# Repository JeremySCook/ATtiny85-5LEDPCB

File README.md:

# ATtiny85-5LEDPCB
PCB with 5 LEDs, different blinking routines for each.

Manual version: https://www.youtube.com/watch?v=wJXMZybXftk

Auto Light-up Wheel light: https://www.youtube.com/watch?v=zVBrc78851Q

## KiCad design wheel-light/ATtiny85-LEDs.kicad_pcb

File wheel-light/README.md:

KiCAD files for new version using SMD components that activates based on bike wheel's rotation.

Works, but could be improved. ICSP header is connected incorrectly, and battery life is somewhat unknown.

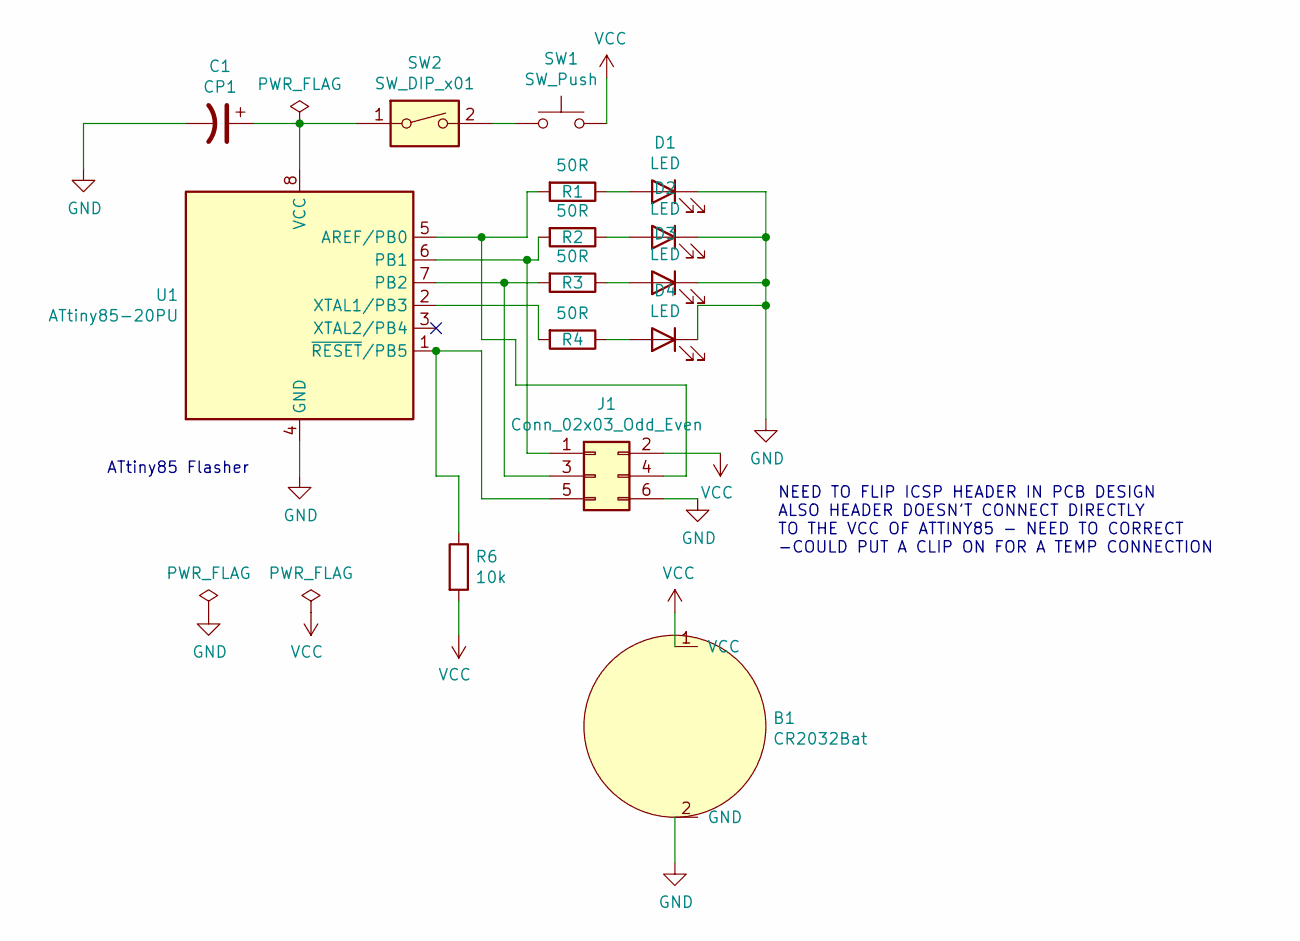
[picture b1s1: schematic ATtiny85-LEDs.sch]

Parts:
B1: CR2032Bat; BatteryHolder_Keystone_3034_1x20mm
C1: CP1; CP_Radial_D8.0mm_P5.00mm
D1, D2, D3, D4: LED; LED_0805_2012Metric
J1: Conn_02x03_Odd_Even; PinHeader_2x03_P2.54mm_Vertical
R1, R2, R3, R4: 50R; R_0805_2012Metric
R6: 10k; R_0805_2012Metric
SW1: SW_Push; CP_Radial_D4.0mm_P1.50mm
SW2: SW_DIP_x01; SW_DIP_SPSTx01_Slide_9.78x4.72mm_W7.62mm_P2.54mm
U1: ATtiny85-20PU; SOIC-8_5.275x5.275mm_P1.27mm

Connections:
GND: B1.2 (GND), C1.2, D1.1 (K), D2.1 (K), D3.1 (K), D4.1 (K), J1.6, U1.4 (GND)
unnamed: C1.1, SW2.1, U1.8 (VCC)
unnamed: D1.2 (A), R1.1
unnamed: D2.2 (A), R2.1
unnamed: D3.2 (A), R3.1
unnamed: D4.2 (A), R4.1
unnamed: J1.1, R2.2, U1.6 (PB1)
unnamed: J1.3, R3.2, U1.7 (PB2)
unnamed: J1.4, R1.2, U1.5 (AREF/PB0)
unnamed: J1.5, R6.1, U1.1 (~RESET~/PB5)
unnamed: R4.2, U1.2 (XTAL1/PB3)
unnamed: SW1.1, SW2.2
VCC: B1.1 (VCC), J1.2, R6.2, SW1.2

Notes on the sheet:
ATtiny85 Flasher
NEED TO FLIP ICSP HEADER IN PCB DESIGN ALSO HEADER DOESN’T CONNECT DIRECTLY TO THE VCC OF ATTINY85 - NEED TO CORRECT -COULD PUT A CLIP ON FOR A TEMP CONNECTION

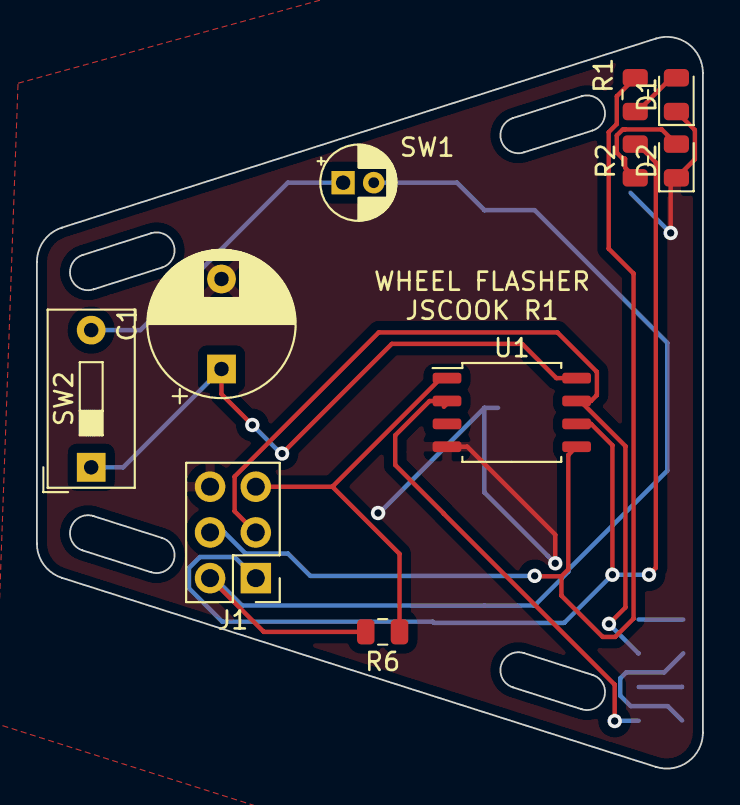
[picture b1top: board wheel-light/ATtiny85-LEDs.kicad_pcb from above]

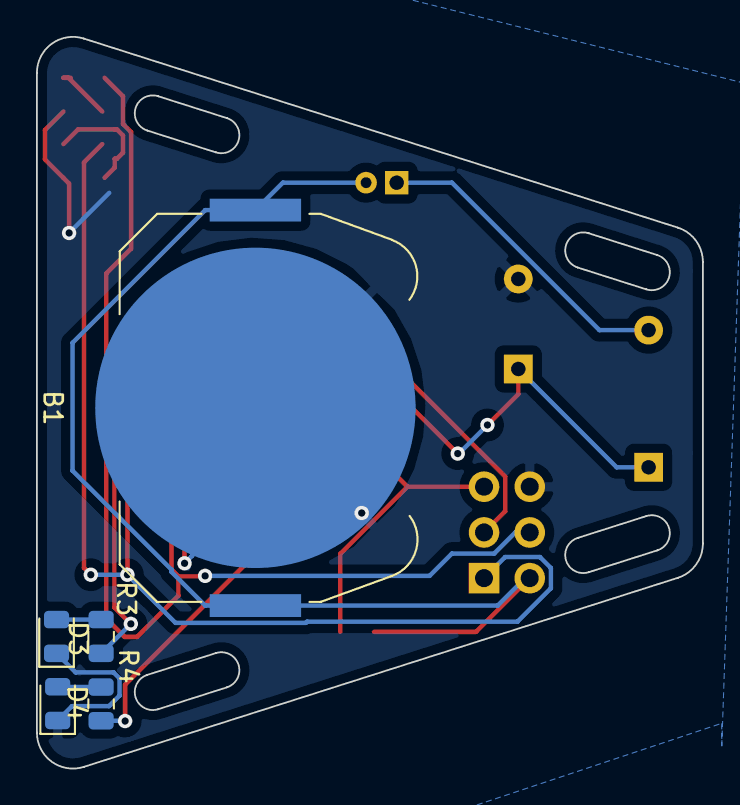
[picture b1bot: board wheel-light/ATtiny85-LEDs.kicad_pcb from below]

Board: 2 copper layers, 37.0 x 40.6 mm, 15 parts (5 on the bottom side), 13 nets.

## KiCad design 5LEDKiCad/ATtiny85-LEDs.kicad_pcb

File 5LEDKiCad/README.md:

Board design. My first PCB - likely could be improved.

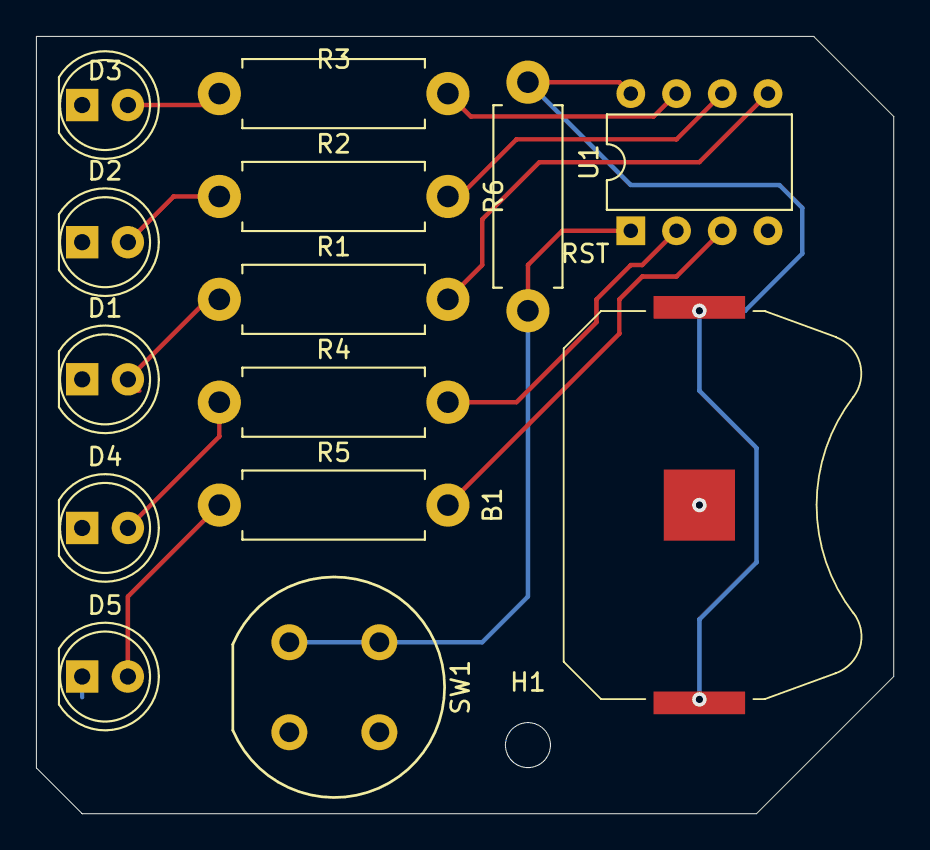
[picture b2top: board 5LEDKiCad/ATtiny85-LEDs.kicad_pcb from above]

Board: 2 copper layers, 47.6 x 43.2 mm, 15 parts (0 on the bottom side), 13 nets.

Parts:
B1: CR2032Bat; BatteryHolder_Keystone_3034_1x20mm
D1, D2, D3, D4, D5: LED; LED_D5.0mm
H1: MountingHole; MountingHole_2.5mm
R1, R2, R3, R4, R5: 50R; R_Axial_DIN0411_L9.9mm_D3.6mm_P12.70mm_Horizontal
R6: 10k; R_Axial_DIN0411_L9.9mm_D3.6mm_P12.70mm_Horizontal
SW1: SW_Push_Dual; Push_E-Switch_KS01Q01
U1: ATtiny85-20PU; DIP-8_W7.62mm

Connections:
GND: B1.2, D1.1, D2.1, D3.1, D4.1, D5.1, SW1.2, SW1.4, U1.4
unnamed: D1.2, R1.1
unnamed: D2.2, R2.1
unnamed: D3.2, R3.1
unnamed: D4.2, R4.1
unnamed: D5.2, R5.1
unnamed: R1.2, U1.5
unnamed: R2.2, U1.6
unnamed: R3.2, U1.7
unnamed: R4.2, U1.2
unnamed: R5.2, U1.3
unnamed: R6.1, SW1.1, SW1.3, U1.1
VCC: B1.1, R6.2, U1.8
